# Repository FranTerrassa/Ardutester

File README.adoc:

:Author: plouc68000
:Email: plouc68000@gmail.com
:Date: 14/10/2018
:Revision: ArduTester V1.13
:License: OSHW

= Project: {Ardutester}

image::pcb delantera.jpg[]

Porting of the files from TransistorTester V1.13 in the Arduino Editor, 
porting first to Arduino Mega, then to Arduino UNO.
The project uses widely the files posted below, same filenames, just .ino files.

https://www.mikrocontroller.net/svnbrowser/transistortester/Software/trunk/

https://github.com/svn2github/transistortester/tree/master/Software/trunk

Description and credits you find here:
https://www.mikrocontroller.net/articles/AVR_Transistortester

También se a consultado este otro link https://www.youtube.com/watch?v=iBbuWZ-2Ljg&t=707s[Mundo Yakara]

== Step 1: Installation

1. Open the file
2. Edit as you like
3. Release to the World!

== Step 2: Assemble the circuit

Assemble the circuit following this instruction:

1. Look at your Arduino/Genuino Uno pins:

-Pin ANALOG IN A0 (PC0) is TP1 ( ArduinoTester Pin 1 )
-Pin ANALOG IN A1 (PC1) is TP2 ( ArduinoTester Pin 2 ) 
-Pin ANALOG IN A2 (PC2) is TP3 ( ArduinoTester Pin 3 )

-Between A0 and DIGITAL 8 (PB0)  connect a 680 Ohm  Resistor
-Between A0 and DIGITAL 9 (PB1)  connect a 470 kOhm Resistor
-Between A1 and DIGITAL 10 (PB2) connect a 680 Ohm  Resistor
-Between A1 and GIGITAL 11 (PB3) connect a 470 kOhm Resistor
-Between A2 and DIGITAL 12 (PB4) connect a 680 Ohm  Resistor
-Between A1 and DIGITAL 13 (PB5) connect a 470 kOhm Resistor

-Pin ANALOG IN A3 to a 10 kOhm pullup Resistor at 5V and via the Test Button to GND

2. Look at your 2 Line LCD HD44780 Compatible ( 4 Bits Data ):

-Connect DIGITAL 5  to LCD DB4
-Connect DIGITAL 4  to LCD DB5
-Connect DIGITAL 3  to LCD DB6
-Connect DIGITAL 2  to LCD DB7
-Connect DIGITAL 7  to LCD RS
-Connect DIGITAL 6  to LCD E

-LCD LED- to GND
-LCD LED+ to 3,3V
-LCD VDD  to 5V
-LCD VSS  to GND
-LCD R/W  to GND
-LCD VO   to 10 kOhm Pot. ( Contrast Adjust. )

== Step 3: Load the code

Select Arduino/Genuino Uno and
Upload the code contained in this sketch on to your board

=== Folder structure

....
 TT_1_13_UNO             => Arduino sketch folder
  ├── TT_13oct.ino       => main Arduino file
  ├── schematics.png     => (optional) if someone wants to do it ...
  ├── layout.png         => (optional) if someone wants to do it ...
  └── ReadMe.adoc        => this file
....

=== License
This project is released under a {OSHW} License.

=== Contributing
To contribute to this project please contact plouc68000 <plouc68000@gmail.com>

=== BOM
Add the bill of the materials you need for this project.

|===
|  ID        |  Part name                | Part number | Quantity |
|            | Pin Header 1x06 2.54mm    |             | 2        |https://es.aliexpress.com/item/32973181162.html?aff_fcid=d903680999de436089a5490bd3a816fa-1727865740130-04704-_op7nKeV&aff_fsk=_op7nKeV&aff_platform=api-new-link-generate&sk=_op7nKeV&aff_trace_key=d903680999de436089a5490bd3a816fa-1727865740130-04704-_op7nKeV&terminal_id=86576b637fb64effa68b8191e53f7e2e&afSmartRedirect=y[Aliexpress]
|  A1        | Arduino Nano USB Mini     |             | 1        |https://es.aliexpress.com/item/1005007066680464.html?spm=a2g0o.productlist.main.1.41e14b2blp1sxW&algo_pvid=47740690-c9e2-45f6-bfde-41709d7d3b26&algo_exp_id=47740690-c9e2-45f6-bfde-41709d7d3b26-0&pdp_npi=4%40dis%21EUR%213.13%212.95%21%21%213.38%213.19%21%40211b617a17278656318553163e50ab%2112000039294978565%21sea%21ES%21110520769%21X&curPageLogUid=RWWmlRxS1obH&utparam-url=scene%3Asearch%7Cquery_from%3A[Aliexpress]
|  U1        | LCD Module 16x2           |             | 1        |https://es.aliexpress.com/item/1005002035425652.html?spm=a2g0o.order_list.order_list_main.161.1501194dUeYPXH&gatewayAdapt=glo2esp[Aliexpress]
|R2-R4,R8-R10| Resistor 680 Ohm SMD 1/4W |             | 3        |https://es.aliexpress.com/item/1005006119604970.html?aff_fcid=109ce6c0f9fc4ad7a73b245d295b5530-1727829901944-07178-_oFS8ZiH&aff_fsk=_oFS8ZiH&aff_platform=api-new-link-generate&sk=_oFS8ZiH&aff_trace_key=109ce6c0f9fc4ad7a73b245d295b5530-1727829901944-07178-_oFS8ZiH&terminal_id=86576b637fb64effa68b8191e53f7e2e&afSmartRedirect=y[Aliexpress]
|R5-R7       | Resistor 240 kOhm SMD 1/4W|             | 6        |https://es.aliexpress.com/item/1005006119604970.html?aff_fcid=109ce6c0f9fc4ad7a73b245d295b5530-1727829901944-07178-_oFS8ZiH&aff_fsk=_oFS8ZiH&aff_platform=api-new-link-generate&sk=_oFS8ZiH&aff_trace_key=109ce6c0f9fc4ad7a73b245d295b5530-1727829901944-07178-_oFS8ZiH&terminal_id=86576b637fb64effa68b8191e53f7e2e&afSmartRedirect=y[Aliexpress]
|  R1        | Resistor 100 kOhm SMD 1/4W|             | 1        |https://es.aliexpress.com/item/1005006119604970.html?aff_fcid=109ce6c0f9fc4ad7a73b245d295b5530-1727829901944-07178-_oFS8ZiH&aff_fsk=_oFS8ZiH&aff_platform=api-new-link-generate&sk=_oFS8ZiH&aff_trace_key=109ce6c0f9fc4ad7a73b245d295b5530-1727829901944-07178-_oFS8ZiH&terminal_id=86576b637fb64effa68b8191e53f7e2e&afSmartRedirect=y[Aliexpress]
|  VR1       | Pot. 200 khm              | T93YB 200K  | 1        |https://www.mouser.es/ProductDetail/Vishay-Sfernice/T93YB-200K-10-TU?qs=BJgd0gnappXpszE2a8ZIhw%3D%3D[Mouser] 
|  SW        | Test Button               |TL2230EEF100 | 1        | https://es.aliexpress.com/item/1703067548.html?aff_fcid=fafa71da58ec4b25b63fa63f5b75399c-1727865206917-02348-_oBVFEtF&aff_fsk=_oBVFEtF&aff_platform=api-new-link-generate&sk=_oBVFEtF&aff_trace_key=fafa71da58ec4b25b63fa63f5b75399c-1727865206917-02348-_oBVFEtF&terminal_id=86576b637fb64effa68b8191e53f7e2e&afSmartRedirect=y[Aliexpress]
|  J2        | Barrel                    |   PJ-002B   | 1        |     https://es.aliexpress.com/item/32974707992.html?spm=a2g0o.order_list.order_list_main.1072.1501194dUeYPXH&gatewayAdapt=glo2esp[Aliexpress]     
|  J1        | Pin Socket 1x03 2.54mm    |             | 1        | https://es.aliexpress.com/item/4001198421663.html?spm=a2g0o.productlist.main.3.54dc1516CoQb6N&algo_pvid=d2288737-30ab-41a3-969c-2ecb81ce213b&algo_exp_id=d2288737-30ab-41a3-969c-2ecb81ce213b-1&pdp_npi=4%40dis%21EUR%211.50%211.47%21%21%211.63%211.60%21%4021038e6617278282349552791e3437%2110000015275671645%21sea%21ES%21110520769%21X&curPageLogUid=Br6Yq0f0jhEw&utparam-url=scene%3Asearch%7Cquery_from%3A[Aliexpress]        
|===

=== Help
This document is written in the _AsciiDoc_ format, a markup language to describe documents. 
If you need help you can search the http://www.methods.co.nz/asciidoc[AsciiDoc homepage]
or consult the http://powerman.name/doc/asciidoc[AsciiDoc cheatsheet]

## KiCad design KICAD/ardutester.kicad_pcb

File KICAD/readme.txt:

Archivos para edición de placa y librerías para este proyecto.

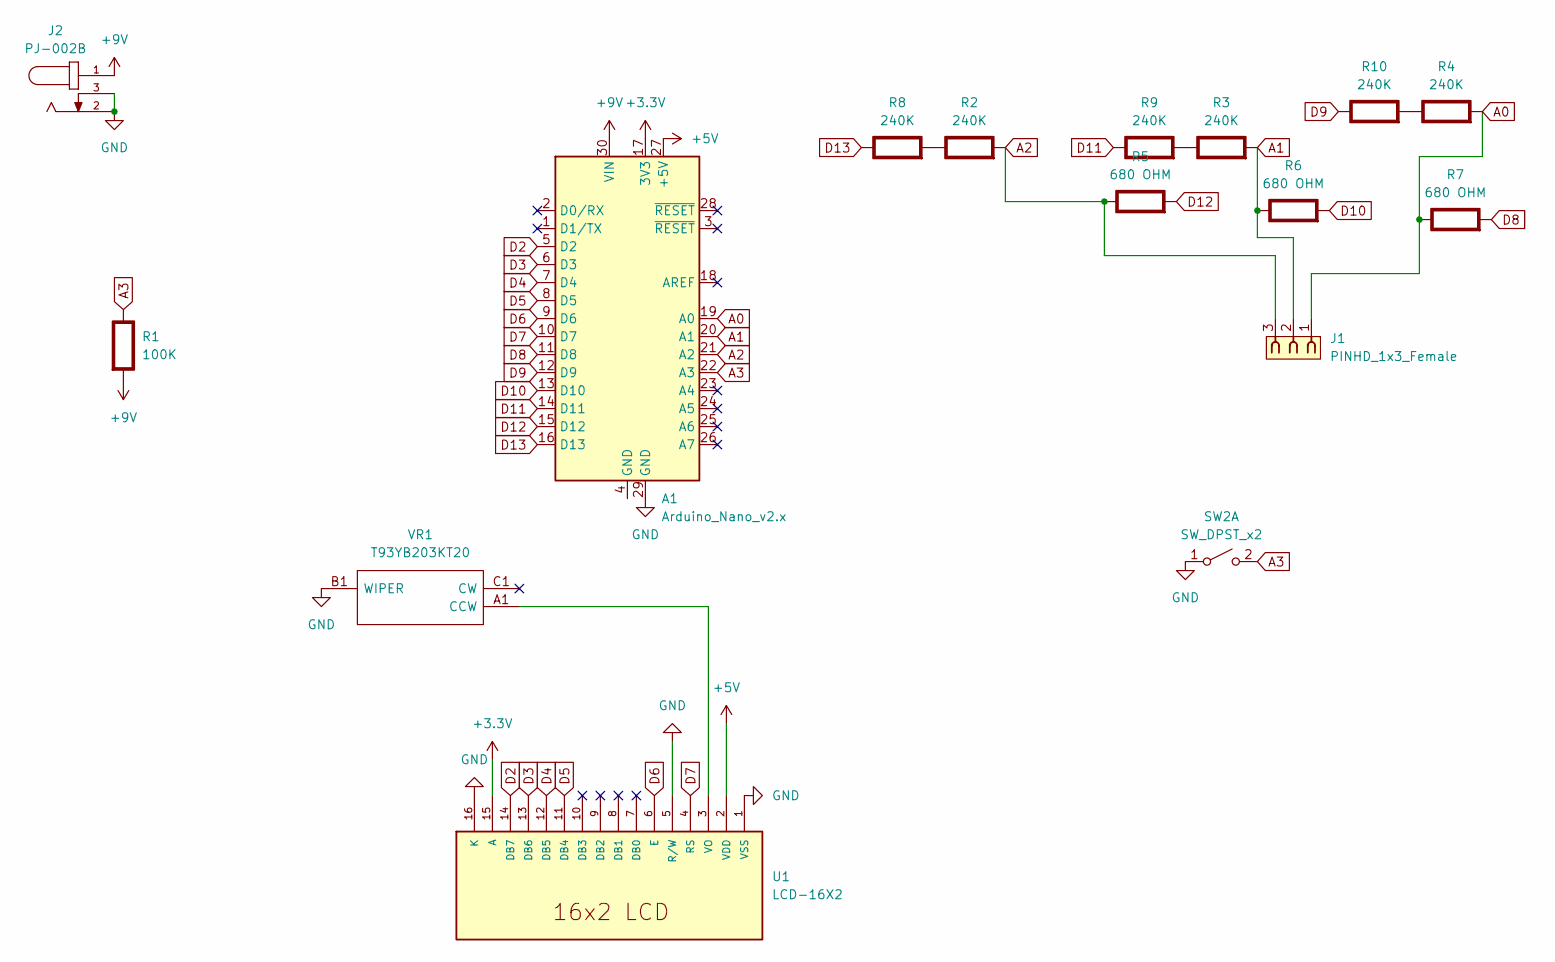
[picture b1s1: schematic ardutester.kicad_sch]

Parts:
A1: Arduino_Nano_v2.x; Arduino_Nano
J1: PINHD_1x3_Female; PinSocket_1x03_P2.54mm_Vertical
J2: PJ-002B; CUI_PJ-002B
R1: 100K; R_1206_3216Metric; Rating W
R2, R3, R4, R8, R9, R10: 240K; R_1206_3216Metric; Rating W
R5, R6, R7: 680 OHM; R_1206_3216Metric; Rating W
SW2: SW_DPST_x2; SW_TL2230EEF100
U1: LCD-16X2; MODULE_LCD-16X2; PARTREV N/A
VR1: T93YB203KT20; Manufacturer_Part_Number T93YB203KT20; Mouser Part Number 72-T93YB-20K

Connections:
+3.3V: A1.17 (3V3), U1.15 (A)
+5V: A1.27 (+5V), U1.2 (VDD)
+9V: A1.30 (VIN), J2.1, R1.2 (-)
A0: A1.19 (A0), J1.1, R4.2 (-), R7.1 (+)
A1: A1.20 (A1), J1.2, R3.2 (-), R6.1 (+)
A2: A1.21 (A2), J1.3, R2.2 (-), R5.1 (+)
A3: A1.22 (A3), R1.1 (+), SW2.2 (B)
D2: A1.5 (D2), U1.14 (DB7)
D3: A1.6 (D3), U1.13 (DB6)
D4: A1.7 (D4), U1.12 (DB5)
D5: A1.8 (D5), U1.11 (DB4)
D6: A1.9 (D6), U1.6 (E)
D7: A1.10 (D7), U1.4 (RS)
D8: A1.11 (D8), R7.2 (-)
D9: A1.12 (D9), R10.1 (+)
D10: A1.13 (D10), R6.2 (-)
D11: A1.14 (D11), R9.1 (+)
D12: A1.15 (D12), R5.2 (-)
D13: A1.16 (D13), R8.1 (+)
GND: A1.29 (GND), J2.2, J2.3, SW2.1 (A), U1.1 (VSS), U1.5 (R/W), U1.16 (K), VR1.B1 (WIPER)
unnamed: R2.1 (+), R8.2 (-)
unnamed: R3.1 (+), R9.2 (-)
unnamed: R4.1 (+), R10.2 (-)
unnamed: U1.3 (VO), VR1.A1 (CCW)

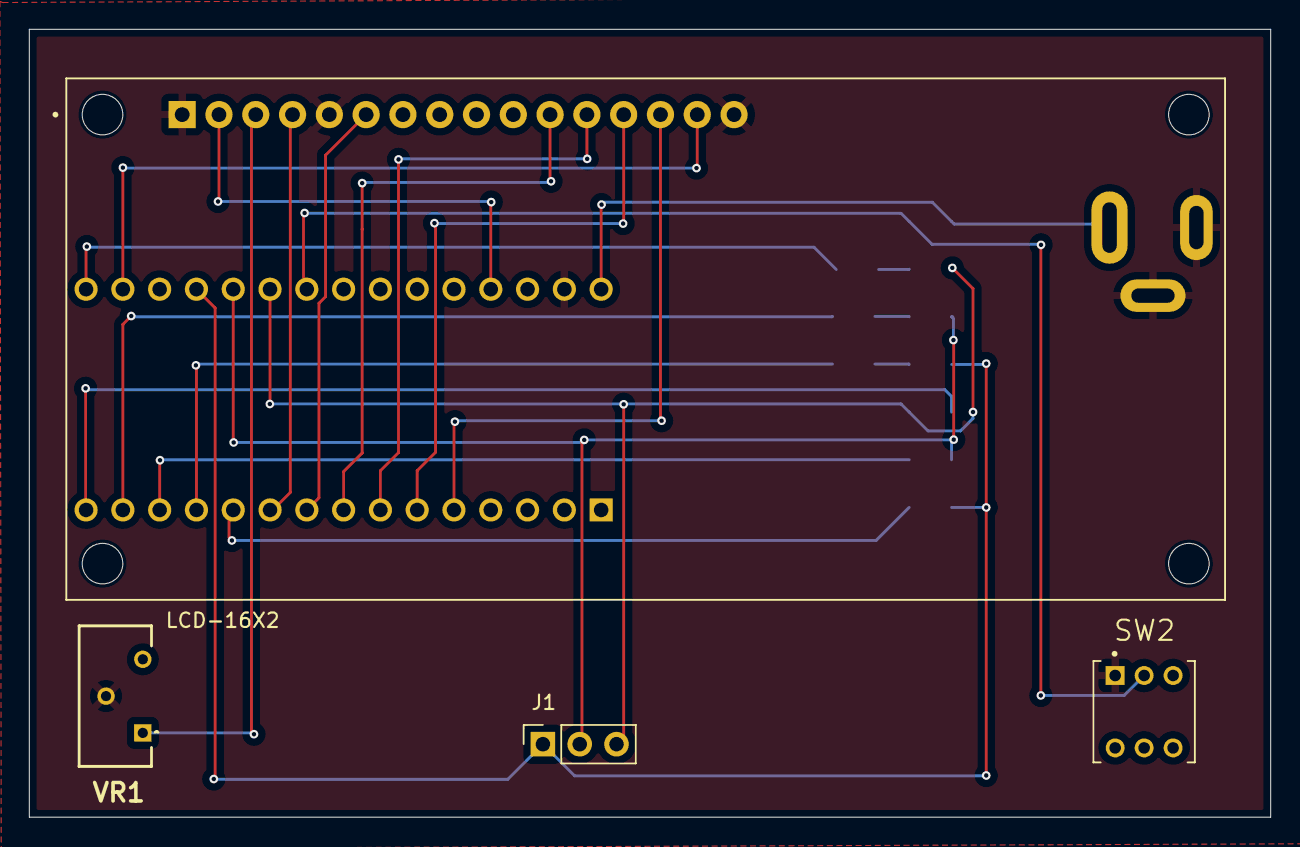
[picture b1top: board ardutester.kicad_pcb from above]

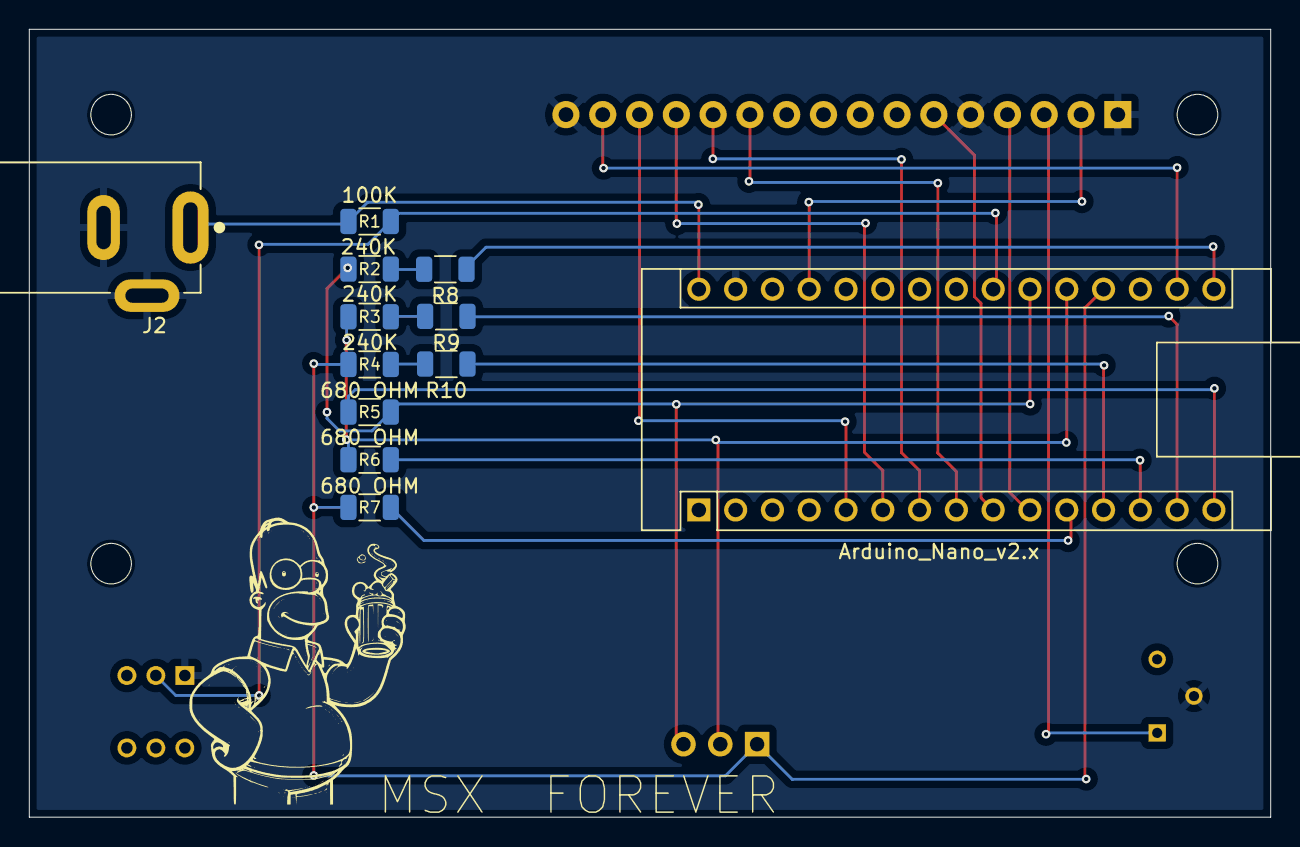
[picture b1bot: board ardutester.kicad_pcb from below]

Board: 2 copper layers, 85.7 x 54.4 mm, 16 parts (12 on the bottom side), 24 nets.

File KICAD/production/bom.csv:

Designator,Footprint,Quantity,Value,LCSC Part #
A1,Arduino_Nano,1,Arduino_Nano_v2.x,
J1,PinSocket_1x03_P2.54mm_Vertical,1,PINHD_1x3_Female,
J2,CUI_PJ-002B,1,PJ-002B,
R1,1206,1,100K,
"R10, R2, R3, R4, R8, R9",1206,6,240K,
"R5, R6, R7",1206,3,680 OHM,
SW2,SW_TL2230EEF100,1,SW_DPST_x2,
U1,MODULE_LCD-16X2,1,LCD-16X2,
VR1,T93YB203KT20,1,T93YB203KT20,

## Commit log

2024-10-01 Case
    Caja diseñada a medida para el circuito
2024-10-01 Caja 3D
    Diseño de caja 3D, para imprimir con boquilla 0.2 y a un 20% de relleno.
2024-10-02 Add files via upload
    Caja 3d diseñada con Tinkercad para Ardutester. Imprimir con boquilla 0.2 a un 20% de relleno.
2024-10-02 Add files via upload
    Código arduino para insertar a Arduino nano
2024-10-02 Add files via upload
    Archivo gerber para la producción de PCB y lista bom. En la lista bom e añadido links para mas fácil adquisición del los componentes, en la resistencia regulable también las hay en aliexpress pero no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
2024-10-02 Rename README.md to README.adoc
2024-10-02 Add files via upload
    Gerber y archivo bom en pdf con links a componentes.
2024-10-02 Add files via upload
    Carpeta de imagenes
2024-11-25 Rename Imagen de WhatsApp 2024-11-25 a las 16.47.15_54525e8f.jpg to trasera pcb montada
